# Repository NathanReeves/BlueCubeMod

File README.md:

# BlueCubeMod

ESP32 based GameCube Controller Bluetooth conversion for Nintendo Switch

v1:
Mac/PC/PS4 supported (tested using Dolphin Emulator on Mac, for Switch/RaspberryPi, use an 8Bitdo USB adapter)

v2: 
Switch support only - no adapter required

## Wiring:

- Connect pins 23 and 18 to GameCube controller's data pin (Red)

- Connect GND to controller's ground pin (Black)

## Build instructions(v2):

- Use this esp-idf fork here: https://github.com/NathanReeves/esp-idf

- Set up the esp-idf environment: https://docs.espressif.com/projects/esp-idf/en/latest/get-started/

- Get the BlueCubeModv2 firmware

- If you haven’t flashed an ESP32 project before, you need the port name of ESP32 for the config file. If using unix system, to get the port name of a USB device run:

`ls /dev`

- Find your device on the list and copy it. It should look something like: /dev/cu.usbserial-DO01EXOV or /dev/cu.SLAB_USBtoUART

- cd into project folder and run:

`make menuconfig`

- Paste your port name into Serial Flasher Config -> Default Serial Port

- Compile and flash the program, run:

`make flash monitor`

Resources used:

http://www.int03.co.uk/crema/hardware/gamecube/gc-control.htm

https://github.com/dekuNukem/Nintendo_Switch_Reverse_Engineering

https://github.com/timmeh87/switchnotes

Thank you to [@Molorius]( https://github.com/Molorius ) for implementing the bluedroid Classic stack for esp

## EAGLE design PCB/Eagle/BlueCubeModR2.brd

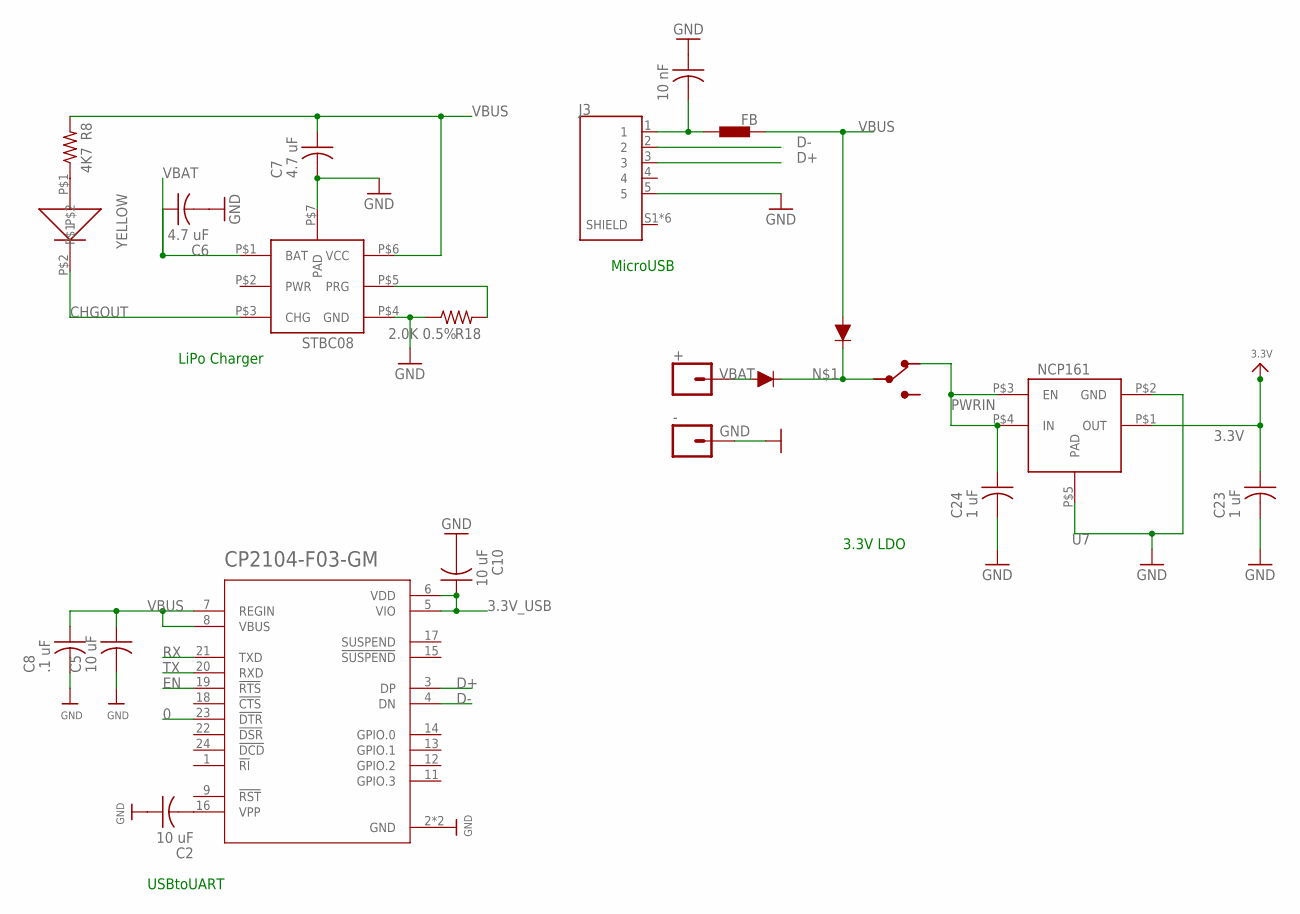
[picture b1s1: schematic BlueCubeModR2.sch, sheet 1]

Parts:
+: CONN_01; 1X01
-: CONN_01; 1X01
C2, C5, C10: 10 uF; C0402_B
C6, C7: 4.7 uF; C0402_B
C8: .1 uF; C0402_B
C11: 10 nF; C0402_B
C23, C24: 1 uF; C0402_B
J3: 2174507-2; J_SMD_2174507-2-5_7.8_5_2.71
L1: FB; 0402
R8: 4K7; R0402_B
R18: 2.0K 0.5%; R0402_B
S2: JS102011JCQN; SW_JS102011JCQN
U2: CP2104-F03-GM; QFN50P400X400X80-25N
U4: STBC08
U7: NCP161
U$4, U$5: DIODD3; DIODFN100X60X30-2
YELLOW: _; 0402LED

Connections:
0: U2.23 (!DTR); also elsewhere on the board
3.3V: C23.1, U7.P$1 (OUT); also elsewhere on the board
3.3V_USB: C10.1, U2.5 (VIO), U2.6 (VDD)
CHGOUT: U4.P$3 (CHG), YELLOW.P$2
D+: J3.3, U2.3 (DP)
D-: J3.2, U2.4 (DN)
EN: U2.19 (!RTS); also elsewhere on the board
GND: -.1, C2.1, C5.2, C6.2, C7.2, C8.2, C10.2, C11.1, C23.2, C24.2, J3.5, R18.1, U2.2 (GND), U2.25 (GND), U4.P$4 (GND), U4.P$7 (PAD), U7.P$2 (GND), U7.P$5 (PAD); also elsewhere on the board
unnamed: S2.2, U$4.2 (C), U$5.2 (C)
unnamed: R8.1, YELLOW.P$1
unnamed: C11.2, J3.1, L1.2
unnamed: C2.2, U2.16 (VPP)
unnamed: R18.2, U4.P$5 (PRG)
PWRIN: C24.1, S2.1, U7.P$3 (EN), U7.P$4 (IN)
RX: U2.21 (TXD); also elsewhere on the board
TX: U2.20 (RXD); also elsewhere on the board
VBAT: +.1, C6.1, U4.P$1 (BAT), U$4.1 (A)
VBUS: C5.1, C7.1, C8.1, L1.1, R8.2, U2.7 (REGIN), U2.8 (VBUS), U4.P$6 (VCC), U$5.1 (A)

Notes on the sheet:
MicroUSB
LiPo Charger
USBtoUART
3.3V LDO

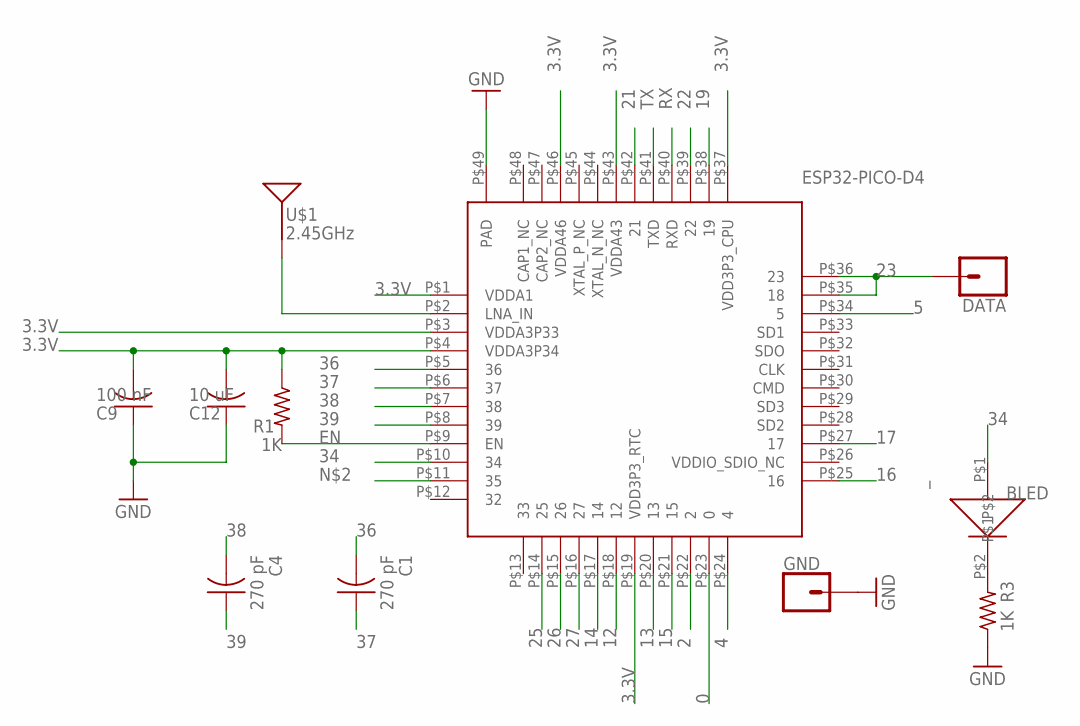
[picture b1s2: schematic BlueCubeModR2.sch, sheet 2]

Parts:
BLED: _; 0402LED
C1, C4: 270 pF; C0402_B
C9: 100 nF; C0402_B
C12: 10 uF; C0402_B
DATA: CONN_01; 1X01
GND: CONN_01; 1X01
R1, R3: 1K; R0402_B
U1: ESP32-PICO-D4
U$1: 2.45GHz; ANT-2.4GHZ-6.5X2.2MM

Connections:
0: U1.P$23 (0); also elsewhere on the board
2: U1.P$22 (2)
3.3V: C9.2, C12.2, R1.1, U1.P$1 (VDDA1), U1.P$3 (VDDA3P33), U1.P$4 (VDDA3P34), U1.P$19 (VDD3P3_RTC), U1.P$37 (VDD3P3_CPU), U1.P$43 (VDDA43), U1.P$46 (VDDA46); also elsewhere on the board
4: U1.P$24 (4)
5: U1.P$34 (5)
12: U1.P$18 (12)
13: U1.P$20 (13)
14: U1.P$17 (14)
15: U1.P$21 (15)
16: U1.P$25 (16)
17: U1.P$27 (17)
19: U1.P$38 (19)
21: U1.P$42 (21)
22: U1.P$39 (22)
23: DATA.1, U1.P$35 (18), U1.P$36 (23)
25: U1.P$14 (25)
26: U1.P$15 (26)
27: U1.P$16 (27)
34: BLED.P$1, U1.P$10 (34)
36: C1.2, U1.P$5 (36)
37: C1.1, U1.P$6 (37)
38: C4.2, U1.P$7 (38)
39: C4.1, U1.P$8 (39)
EN: R1.2, U1.P$9 (EN); also elsewhere on the board
ESPANT: U1.P$2 (LNA_IN), U$1.FEED
GND: C9.1, C12.1, GND.1, R3.1, U1.P$49 (PAD); also elsewhere on the board
unnamed: BLED.P$2, R3.2
RX: U1.P$40 (RXD); also elsewhere on the board
TX: U1.P$41 (TXD); also elsewhere on the board

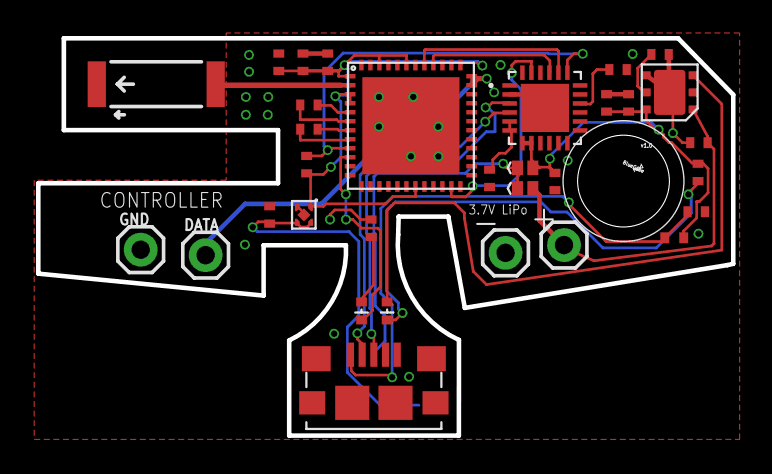
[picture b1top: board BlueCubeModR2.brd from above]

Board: 4 copper layers, 38.6 x 22.1 mm, 33 parts (1 on the bottom side), 26 nets.

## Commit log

2019-04-29 added firmware
2019-04-29 added .gitignore
2019-05-02 added board files
2020-02-01 Added v2 firmware w/ switch support
    see updated readme for new build instructions
2020-02-19 compile error fix
2020-02-21 updated readme
    +started modding resources folder
2020-02-27 added pics to readme
2020-02-27 fixed reboot loop
2020-04-28 Change Grip/Order menu stays open on connect
2020-04-29 store a random mac address in flash
    Allows multiple controllers on one switch console
2020-04-29 put random bt addr in switch packet
2020-06-26 add license
2021-11-27 fixed v2 firmware to work using latest esp_idf
2022-12-30 Add files via upload
    I've added the BOM and Centroid files based on the Eagle files so people in the future don't need to request them or create them.

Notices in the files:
parts and their libraries:
SparkFun-Connectors: Licensing: Creative Commons ShareAlike 4.0 International - https://creativecommons.org/licenses/by-sa/4.0
SparkFun-Aesthetics: Licensing: CC v3.0 Share-Alike You are welcome to use this library for commercial purposes.
